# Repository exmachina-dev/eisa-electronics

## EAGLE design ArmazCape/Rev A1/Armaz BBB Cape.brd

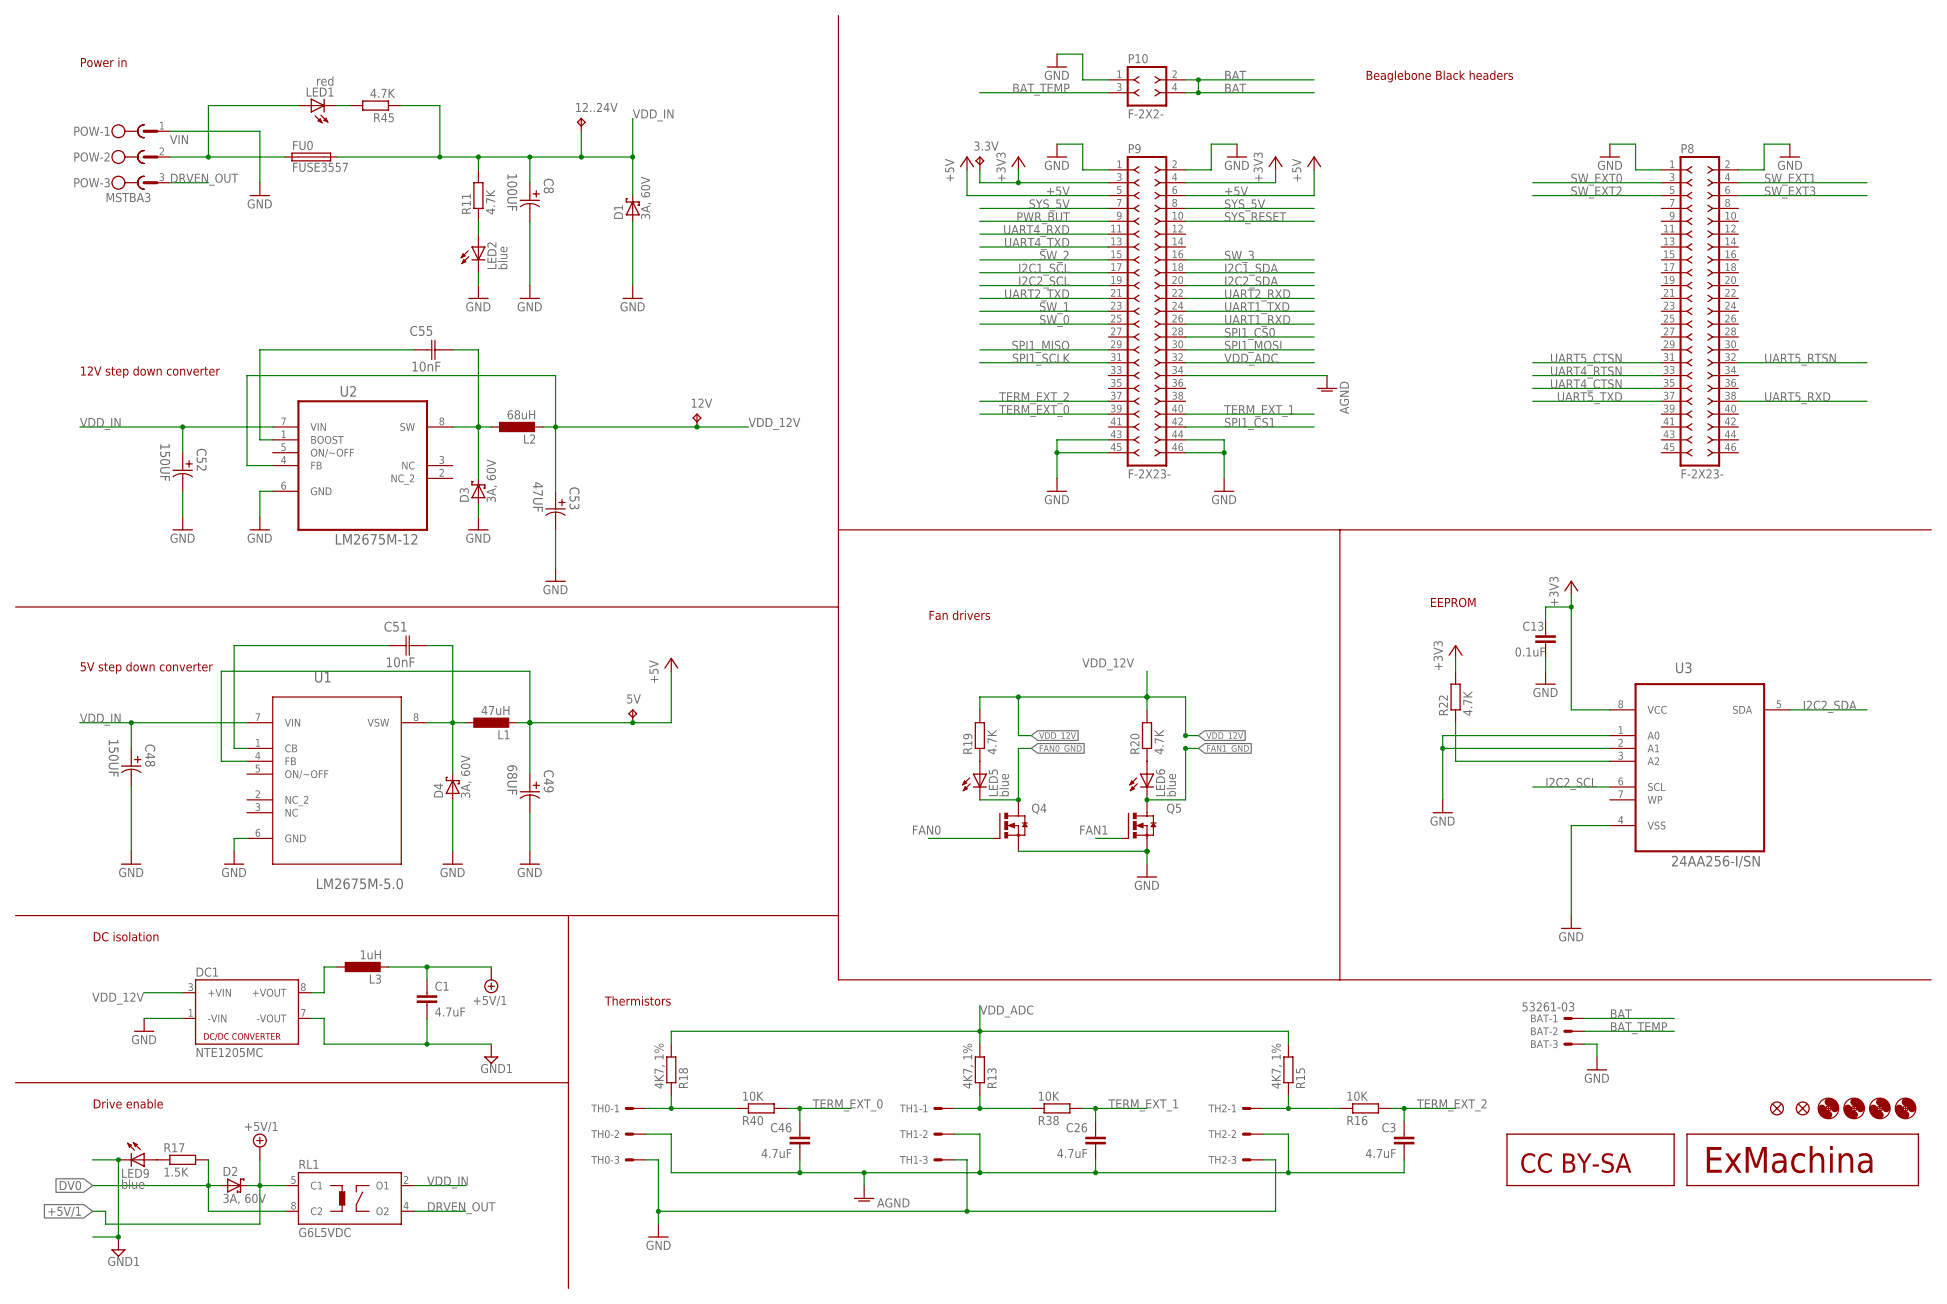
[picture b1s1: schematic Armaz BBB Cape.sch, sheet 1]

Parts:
3.3V, 5V, 12..24V, 12V: TPB1,27; B1,27
BAT: 53261-03; MPN 53261-0371
C1: 4.7uF; C0805; MPN MC0805X475K6R3CT
C3, C26, C46: 4.7uF; C0402; MPN MC0603X475K6R3CT
C8: 100UF; CAPAE660X800N; MPN EEEFTH101XAP
C13: 0.1uF; C0402; MPN MC0402B104K160CT
C48, C52: 150UF; CAPAE660X800N; MPN EEEFTV151XAP
C49: 68UF; CAPAE430X610N; MPN EEEFT1A680AR
C51, C55: 10nF; CAPC2013X90N; MPN MCU0805R103KCT
C53: 47UF; CAPAE530X610N; MPN EEEFT1E470AR
D1, D2, D3, D4: 3A, 60V; SMB
DC1: NTE1205MC; NTE; MPN NTE1205MC
FU0: FUSE3557; 3557; MPN 3557
H1, H2, H3, H4: MOUNT-HOLE3.3; 3,3
JP1, JP2: FIDUCIAL1X2; FIDUCIAL-1X2
L1: 47uH; B82462G4; MPN B82462G4473M
L2: 68uH; B82462G4; MPN B82462G4683M
L3: 1uH; B82462G4; MPN B82462G4102M
LED1: red; CHIP-LED0603; MPN OVS-0608
LED2, LED5, LED6, LED9: blue; CHIP-LED0603; MPN OVS-0603
P8, P9: F-2X23-; DIL-100-2X23; MPN ESQ-123-14-T-D
P10: F-2X2-; DIL-100-2X2; MPN TSW-104-14-T-D
POW: MSTBA3
Q4, Q5: IRLML6344TRPBF; SOT95P240X112-3N
R11, R19, R20, R22, R45: 4.7K; R0402; MPN MCMR04X4701FTL
R13, R15, R18: 4K7, 1%; R0402; MPN MCMR04X4701FTL
R16, R38, R40: 10K; R0402; MPN MCMR04X1002FTL
R17: 1.5K; R0402; MPN MCMR04X1501FTL
RL1: G6L5VDC; G6L-1F; MPN G6L1F5DC
TH0, TH1, TH2: 22-05-7038-03; 7395-03; MPN 22-05-7038
U1: LM2675M-5.0; SOIC127P620X175-8N
U2: LM2675M-12; SOIC127P600X175-8N; MPN LM2675M-12/NOPB
U3: 24AA256-I/SN; SOIC127P600X175-8N
U$1: EXMACHINA-LOGO; EXM-LOGO
U$2: CC-BY-SA

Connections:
$1: C51.1 (C1), U1.1 (CB)
+3V3: 3.3V.TP, C13.1, P9.3, P9.4, R22.2, U3.8 (VCC); also elsewhere on the board
+5V: 5V.TP, C49.1, L1.2, P9.5, P9.6, U1.4 (FB); also elsewhere on the board
+5V/1: C1.1, D2.C, L3.2, RL1.5 (C1); also elsewhere on the board
AGND: C3.2, C26.2, C46.2, P9.34, TH0.2, TH1.2, TH2.2
BAT: BAT.1, P10.2, P10.4
BAT_TEMP: BAT.2, P10.3
DRVEN_OUT: POW.3, RL1.4 (O2)
DV0: D2.A, R17.2, RL1.8 (C2); also elsewhere on the board
FAN0: Q4.1 (G); also elsewhere on the board
FAN0_GND: LED5.C, Q4.3 (D); also elsewhere on the board
FAN1: Q5.1 (G); also elsewhere on the board
FAN1_GND: LED6.C, Q5.3 (D); also elsewhere on the board
GND: BAT.3, C8.2, C13.2, C48.2, C49.2, C52.2, C53.2, D1.A, D3.A, D4.A, DC1.1 (-VIN), LED2.C, P8.1, P8.2, P9.1, P9.2, P9.43, P9.44, P9.45, P9.46, P10.1, POW.1, Q4.2 (S), Q5.2 (S), TH0.3, TH1.3, TH2.3, U2.6 (GND), U3.1 (A0), U3.2 (A1), U3.4 (VSS); also elsewhere on the board
GND1: C1.2, DC1.7 (-VOUT), LED9.C; also elsewhere on the board
I2C1_SCL: P9.17
I2C1_SDA: P9.18
I2C2_SCL: P9.19, U3.6 (SCL); also elsewhere on the board
I2C2_SDA: P9.20, U3.5 (SDA); also elsewhere on the board
unnamed: LED9.A, R17.1
unnamed: LED1.C, R45.2
unnamed: LED5.A, R19.1
unnamed: DC1.8 (+VOUT), L3.1
unnamed: R15.1, R16.1, TH2.1
unnamed: LED2.A, R11.1
unnamed: LED6.A, R20.1
unnamed: R22.1, U3.3 (A2)
unnamed: R13.1, R38.1, TH1.1
unnamed: R18.1, R40.1, TH0.1
unnamed: C55.1 (C1), U2.1 (BOOST)
PWR_BUT: P9.9
SPI1_CS0: P9.28; also elsewhere on the board
SPI1_CS1: P9.42
SPI1_MISO: P9.29; also elsewhere on the board
SPI1_MOSI: P9.30; also elsewhere on the board
SPI1_SCLK: P9.31; also elsewhere on the board
SW: C51.2 (C2), D4.C, L1.1, U1.8 (VSW)
SW_0: P9.25; also elsewhere on the board
SW_1: P9.23; also elsewhere on the board
SW_2: P9.15; also elsewhere on the board
SW_3: P9.16; also elsewhere on the board
SW_12V: C55.2 (C2), D3.C, L2.1, U2.8 (SW)
SW_EXT0: P8.3; also elsewhere on the board
SW_EXT1: P8.4; also elsewhere on the board
SW_EXT2: P8.5; also elsewhere on the board
SW_EXT3: P8.6; also elsewhere on the board
SYS_5V: P9.7, P9.8; also elsewhere on the board
SYS_RESET: P9.10; also elsewhere on the board
TERM_EXT_0: C46.1, P9.39, R40.2
TERM_EXT_1: C26.1, P9.40, R38.2
TERM_EXT_2: C3.1, P9.37, R16.2
UART1_RXD: P9.26
UART1_TXD: P9.24
UART2_RXD: P9.22
UART2_TXD: P9.21
UART4_CTSN: P8.35
UART4_RTSN: P8.33
UART4_RXD: P9.11; also elsewhere on the board
UART4_TXD: P9.13
UART5_CTSN: P8.31
UART5_RTSN: P8.32
UART5_RXD: P8.38; also elsewhere on the board
UART5_TXD: P8.37; also elsewhere on the board
VDD_12V: 12V.TP, C53.1, DC1.3 (+VIN), L2.2, R19.2, R20.2, U2.4 (FB); also elsewhere on the board
VDD_ADC: P9.32, R13.2, R15.2, R18.2
VDD_IN: 12..24V.TP, C8.1, C48.1, C52.1, D1.C, FU0.3 (2), FU0.4 (2), R11.2, R45.1, RL1.2 (O1), U1.7 (VIN), U2.7 (VIN)
VIN: FU0.1, FU0.2 (1), LED1.A, POW.2

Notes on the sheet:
5V step down converter
Power in
12V step down converter
EEPROM
Fan drivers
Thermistors
Drive enable
DC isolation
Beaglebone Black headers

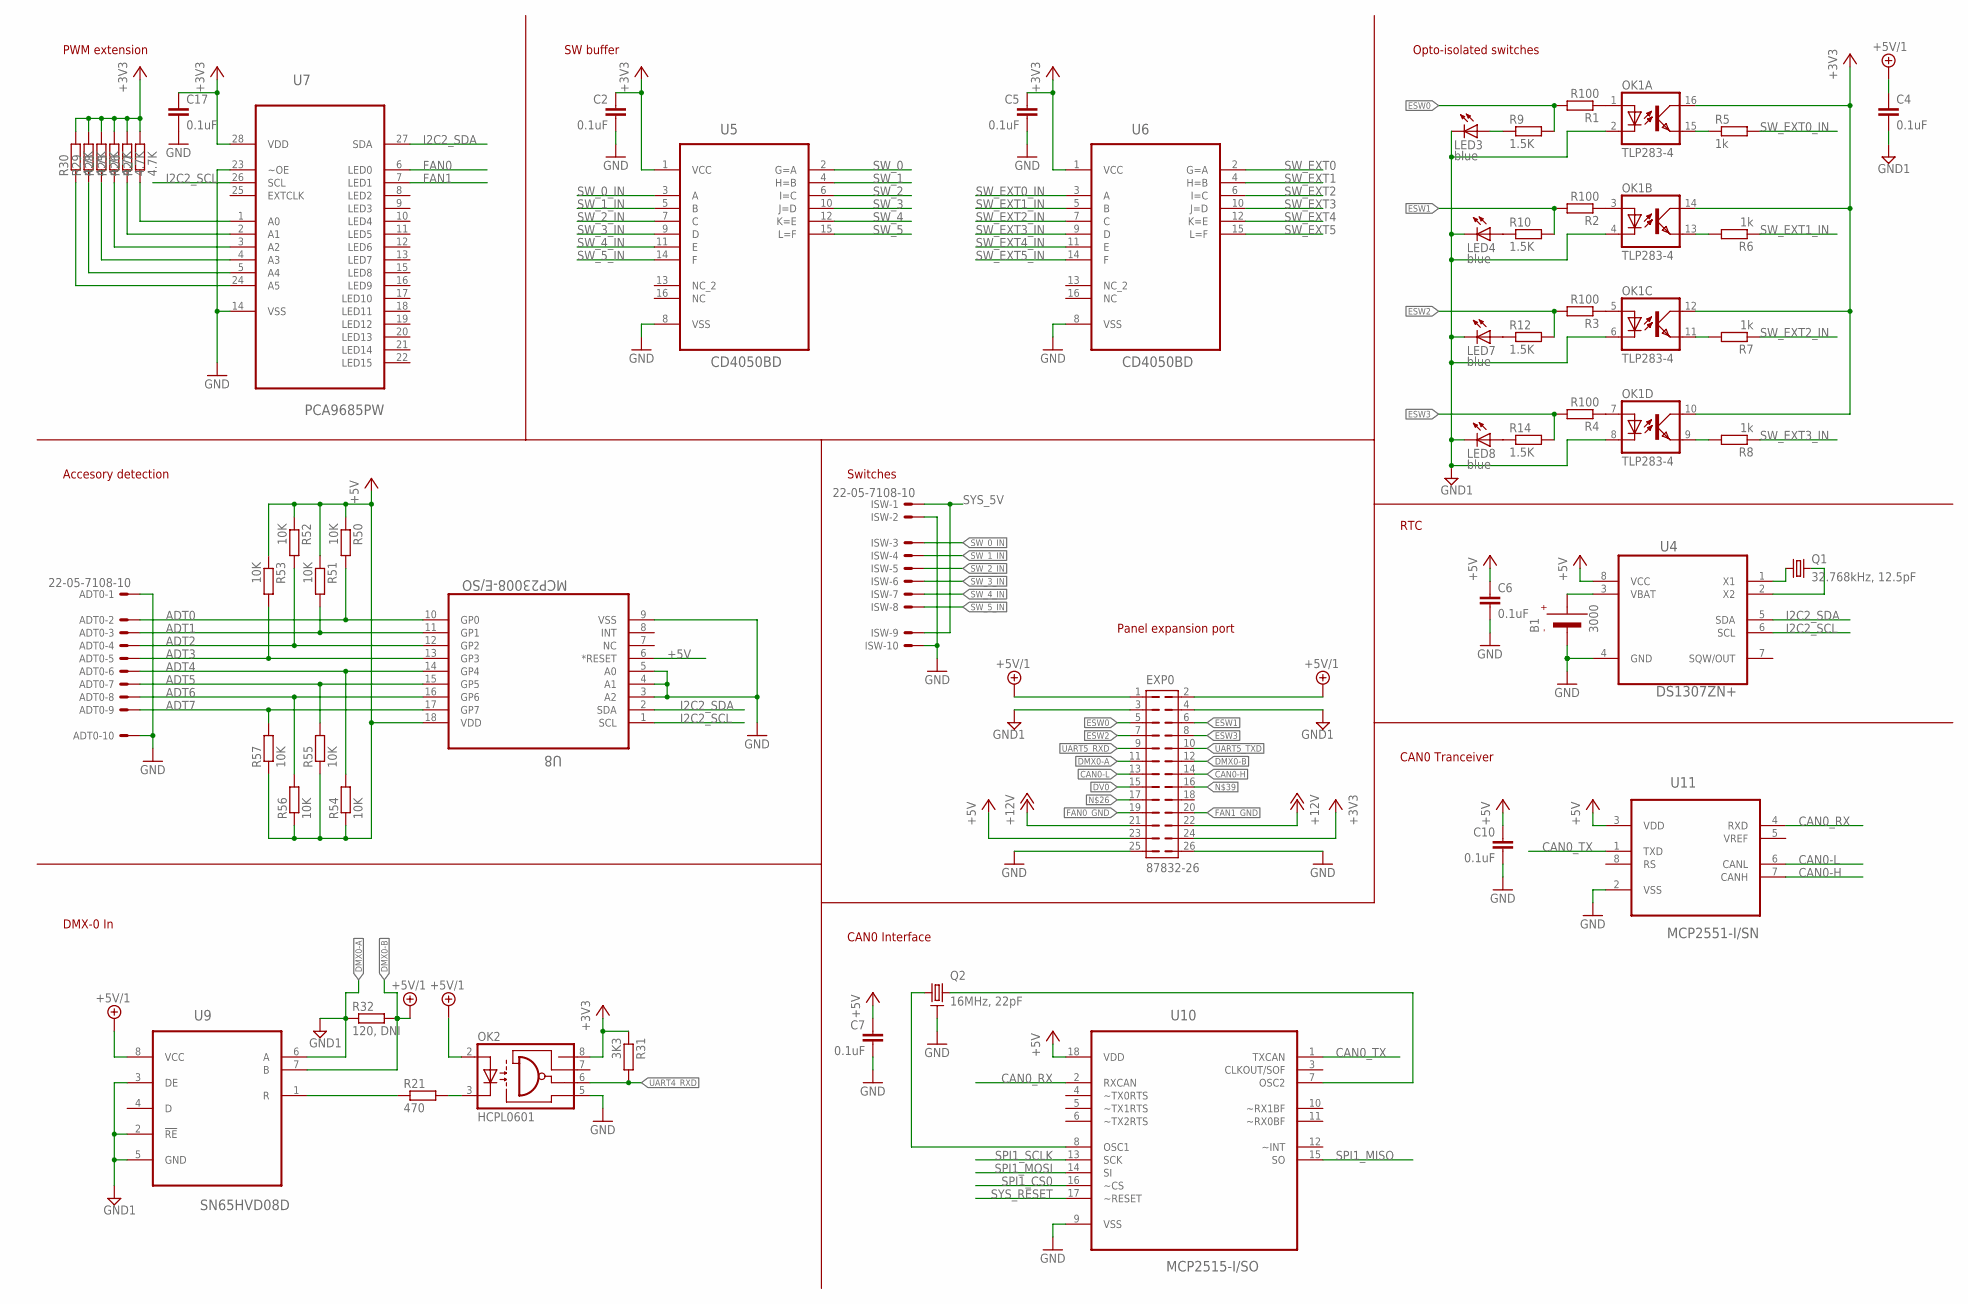
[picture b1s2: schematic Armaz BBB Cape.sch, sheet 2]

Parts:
ADT0: 22-05-7108-10; 7395-10; MPN 22-05-7108
B1: 3000; MPN 3000
C2, C4, C5, C6, C7, C10, C17: 0.1uF; C0402; MPN MC0402B104K160CT
EXP0: 87832-26; MPN 87832-2620
ISW: 22-05-7108-10; 7395-10; MPN 22-05-7108
LED3, LED4, LED7, LED8: blue; CHIP-LED0603; MPN OVS-0603
OK1: TLP283-4; MINI-FLAT-16; MPN TCMT4100
OK2: HCPL0601; SOIC08
Q1: 32.768kHz, 12.5pF; ABS07; MPN ABS07-32.768KHZ-T
Q2: 16MHz, 22pF; AWSCR-MT; MPN AWSCR-16.00MTD-T
R1, R2, R3, R4: R100; R0402; MPN MCMR04X1000FTL
R5, R6, R7, R8: 1k; R0402; MPN MCMR04X1001FTL
R9, R10, R12, R14: 1.5K; R0402; MPN MCMR04X1501FTL
R21: 470; R0402; MPN MCMR04X4700FTL
R25, R26, R27, R28, R29, R30: 4.7K; R0402; MPN MCMR04X4701FTL
R31: 3K3; R0402; MPN MCMR04X3301FTL
R32: 120, DNI; R0402; MPN MCMR04X1200FTL
R50, R51, R52, R53, R54, R55, R56, R57: 10K; R0402; MPN MCMR04X1002FTL
U4: DS1307ZN+; SOIC127P600X175-8N
U5, U6: CD4050BD; SOIC127P600X175-16N
U7: PCA9685PW; SOP65P640X110-28N
U8: MCP23008-E/SO; SOIC127P1030X265-18N
U9: SN65HVD08D; SOIC127P600X175-8N
U10: MCP2515-I/SO; SOIC127P1034X264-18N
U11: MCP2551-I/SN; SOIC127P600X175-8N

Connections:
+3V3: C2.1, C5.1, C17.1, EXP0.24, OK1.10 (COL), OK1.12 (COL), OK1.14 (COL), OK1.16 (COL), OK2.8 (VCC), R25.2, R26.2, R27.2, R28.2, R29.2, R30.2, R31.1, U5.1 (VCC), U6.1 (VCC), U7.28 (VDD); also elsewhere on the board
+5V: C6.1, C7.1, C10.1, EXP0.23, R50.1, R51.1, R52.1, R53.1, R54.1, R55.1, R56.1, R57.1, U4.8 (VCC), U8.6 (*RESET), U8.18 (VDD), U10.18 (VDD), U11.3 (VDD); also elsewhere on the board
+5V/1: C4.1, EXP0.1, EXP0.2, OK2.2 (A), U9.8 (VCC); also elsewhere on the board
ADT0: ADT0.2, R50.2, U8.10 (GP0)
ADT1: ADT0.3, R51.2, U8.11 (GP1)
ADT2: ADT0.4, R52.2, U8.12 (GP2)
ADT3: ADT0.5, R53.2, U8.13 (GP3)
ADT4: ADT0.6, R54.2, U8.14 (GP4)
ADT5: ADT0.7, R55.2, U8.15 (GP5)
ADT6: ADT0.8, R56.2, U8.16 (GP6)
ADT7: ADT0.9, R57.2, U8.17 (GP7)
CAN0-H: EXP0.14, U11.7 (CANH)
CAN0-L: EXP0.13, U11.6 (CANL)
CAN0_RX: U10.2 (RXCAN), U11.4 (RXD)
CAN0_TX: U10.1 (TXCAN), U11.1 (TXD)
DMX0-A: EXP0.11, R32.1, U9.6 (A)
DMX0-B: EXP0.12, R32.2, U9.7 (B)
DV0: EXP0.15; also elsewhere on the board
ESW0: EXP0.5, R1.2, R9.2
ESW1: EXP0.6, R2.2, R10.2
ESW2: EXP0.7, R3.2, R12.2
ESW3: EXP0.8, R4.2, R14.2
FAN0: U7.6 (LED0); also elsewhere on the board
FAN0_GND: EXP0.19; also elsewhere on the board
FAN1: U7.7 (LED1); also elsewhere on the board
FAN1_GND: EXP0.20; also elsewhere on the board
GND: ADT0.1, ADT0.10, B1.- (VBAT-), C2.2, C5.2, C6.2, C7.2, C10.2, C17.2, EXP0.25, EXP0.26, ISW.2, ISW.10, OK2.5 (GND), Q2.2, U4.4 (GND), U5.8 (VSS), U6.8 (VSS), U7.14 (VSS), U7.23 (~OE), U8.3 (A2), U8.4 (A1), U8.5 (A0), U8.9 (VSS), U10.9 (VSS), U11.2 (VSS); also elsewhere on the board
GND1: C4.2, EXP0.3, EXP0.4, LED3.C, LED4.C, LED7.C, LED8.C, OK1.2 (C), OK1.4 (C), OK1.6 (C), OK1.8 (C), U9.2 (!RE), U9.3 (DE), U9.5 (GND); also elsewhere on the board
I2C2_SCL: U4.6 (SCL), U7.26 (SCL), U8.1 (SCL); also elsewhere on the board
I2C2_SDA: U4.5 (SDA), U7.27 (SDA), U8.2 (SDA); also elsewhere on the board
unnamed: OK1.1 (A), R1.1
unnamed: OK1.3 (A), R2.1
unnamed: OK1.15 (EMIT), R5.1
unnamed: OK1.7 (A), R4.1
unnamed: Q1.P$1 (1), U4.1 (X1)
unnamed: OK1.5 (A), R3.1
unnamed: Q1.P$2 (2), U4.2 (X2)
unnamed: R21.1, U9.1 (R)
unnamed: OK1.9 (EMIT), R8.2
unnamed: OK1.11 (EMIT), R7.2
unnamed: OK1.13 (EMIT), R6.2
unnamed: LED3.A, R9.1
unnamed: OK2.3 (C), R21.2
unnamed: LED4.A, R10.1
unnamed: LED7.A, R12.1
unnamed: LED8.A, R14.1
unnamed: Q2.3, U10.7 (OSC2)
unnamed: Q2.1, U10.8 (OSC1)
unnamed: R27.1, U7.1 (A0)
unnamed: R26.1, U7.2 (A1)
unnamed: R25.1, U7.3 (A2)
unnamed: R28.1, U7.4 (A3)
unnamed: R29.1, U7.5 (A4)
unnamed: R30.1, U7.24 (A5)
SPI1_CS0: U10.16 (~CS); also elsewhere on the board
SPI1_MISO: U10.15 (SO); also elsewhere on the board
SPI1_MOSI: U10.14 (SI); also elsewhere on the board
SPI1_SCLK: U10.13 (SCK); also elsewhere on the board
SW_0: U5.2 (G=A); also elsewhere on the board
SW_0_IN: ISW.3, U5.3 (A)
SW_1: U5.4 (H=B); also elsewhere on the board
SW_1_IN: ISW.4, U5.5 (B)
SW_2: U5.6 (I=C); also elsewhere on the board
SW_2_IN: ISW.5, U5.7 (C)
SW_3: U5.10 (J=D); also elsewhere on the board
SW_3_IN: ISW.6, U5.9 (D)
SW_4: U5.12 (K=E)
SW_4_IN: ISW.7, U5.11 (E)
SW_5: U5.15 (L=F)
SW_5_IN: ISW.8, U5.14 (F)
SW_EXT0: U6.2 (G=A); also elsewhere on the board
SW_EXT0_IN: R5.2, U6.3 (A)
SW_EXT1: U6.4 (H=B); also elsewhere on the board
SW_EXT1_IN: R6.1, U6.5 (B)
SW_EXT2: U6.6 (I=C); also elsewhere on the board
SW_EXT2_IN: R7.1, U6.7 (C)
SW_EXT3: U6.10 (J=D); also elsewhere on the board
SW_EXT3_IN: R8.1, U6.9 (D)
SW_EXT4: U6.12 (K=E)
SW_EXT4_IN: U6.11 (E)
SW_EXT5: U6.15 (L=F)
SW_EXT5_IN: U6.14 (F)
SYS_5V: ISW.1, ISW.9; also elsewhere on the board
SYS_RESET: U10.17 (~RESET); also elsewhere on the board
UART4_RXD: OK2.6 (VO), R31.2; also elsewhere on the board
UART5_RXD: EXP0.9; also elsewhere on the board
UART5_TXD: EXP0.10; also elsewhere on the board
VBAT+: B1.+1 (VBAT+), B1.+2 (VBAT+), U4.3 (VBAT)
VDD_12V: EXP0.21, EXP0.22; also elsewhere on the board

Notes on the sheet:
Switches
PWM extension
SW buffer
Accesory detection
Opto-isolated switches
Panel expansion port
DMX-0 In
RTC
CAN0 Interface
CAN0 Tranceiver

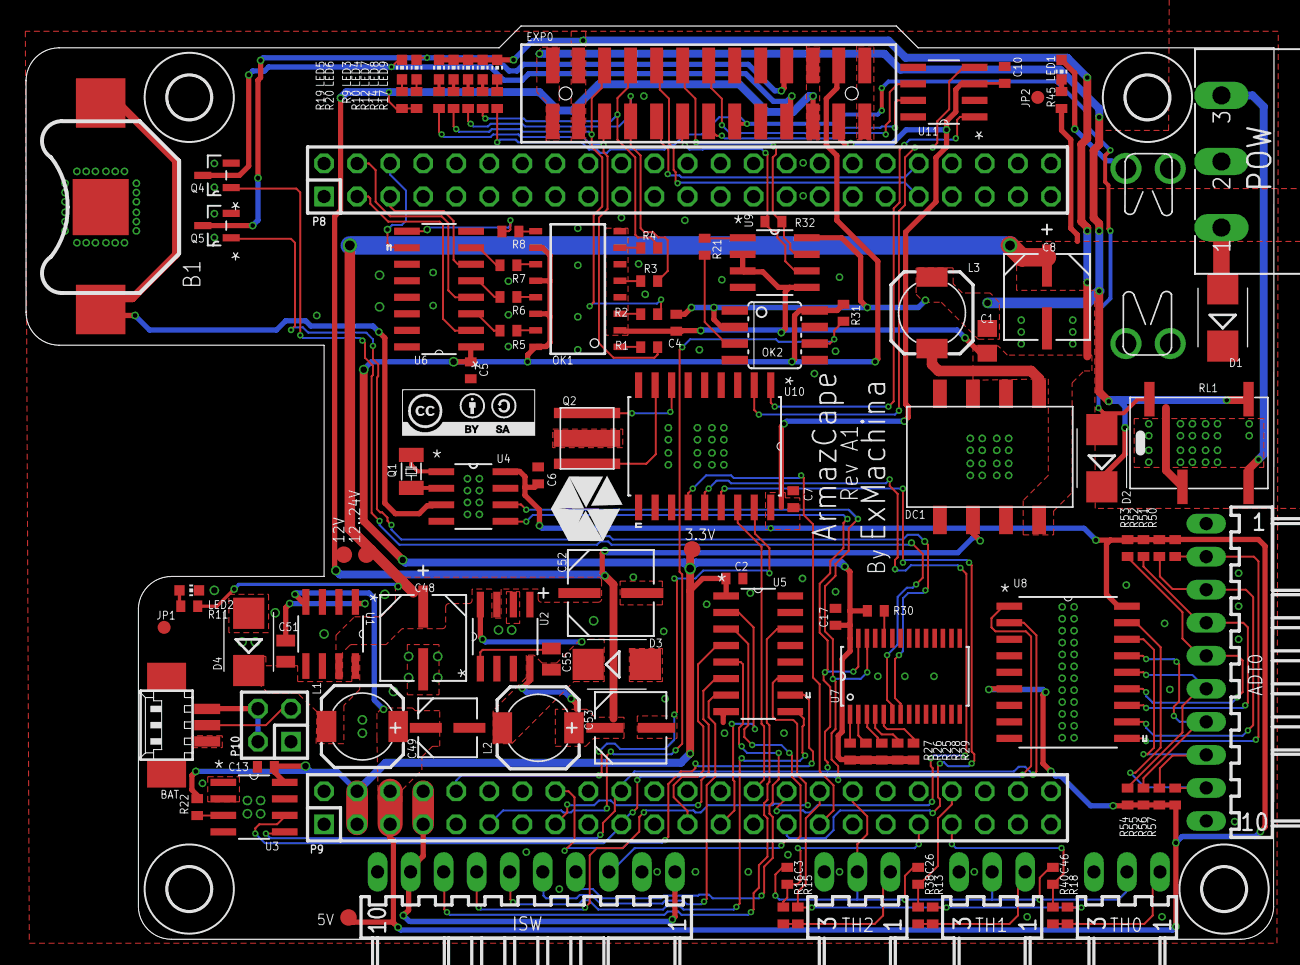
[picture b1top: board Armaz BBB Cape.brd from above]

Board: 2 copper layers, 95.9 x 70.2 mm, 120 parts (0 on the bottom side), 107 nets.

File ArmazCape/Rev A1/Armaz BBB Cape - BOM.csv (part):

"Part";"Value";"Device";"Package";"Description";"MF";"MPN";"OC_FARNELL";"OC_NEWARK";"PACKAGE";"SUPPLIER";"TOLERANCE";"TP_SIGNAL_NAME";"VALUE";"VOLTAGERATING";
"3.3V";"TPB1,27";"TPB1,27";"B1,27";"Test pad";"";"";"unknown";"";"";"";"";"";"";"";
"5V";"TPB1,27";"TPB1,27";"B1,27";"Test pad";"";"";"unknown";"";"";"";"";"";"";"";
"12..24V";"TPB1,27";"TPB1,27";"B1,27";"Test pad";"";"";"unknown";"";"";"";"";"";"";"";
"12V";"TPB1,27";"TPB1,27";"B1,27";"Test pad";"";"";"unknown";"";"";"";"";"";"";"";
"ADT0";"22-05-7108-10";"22-05-7108-10";"7395-10";"CONNECTOR";"MOLEX";"22-05-7108";"9731660";"unknown";"";"";"";"";"";"";
"B1";"3000";"3000";"3000";"";"KEYSTONE";"3000";"1650692";"";"";"";"";"";"";"";
"BAT";"53261-03";"53261-03";"53261-03";"CONNECTOR";"MOLEX";"53261-0371";"1125359";"57H5006";"";"";"";"";"";"";
"C1";"4.7uF";"C-EUC0805";"C0805";"CAPACITOR, European symbol";"MULTICOMP";"MC0805X475K6R3CT";"1759414";"";"";"";"";"";"";"";
"C2";"0.1uF";"C-EUC0402";"C0402";"CAPACITOR, European symbol";"MULTICOMP";"MC0402B104K160CT";"1758896";"";"";"";"";"";"";"";
"C3";"4.7uF";"C-EUC0402";"C0402";"CAPACITOR, European symbol";"MULTICOMP";"MC0603X475K6R3CT";"2320811";"";"";"";"";"";"";"";
"C4";"0.1uF";"C-EUC0402";"C0402";"CAPACITOR, European symbol";"MULTICOMP";"MC0402B104K160CT";"1758896";"";"";"";"";"";"";"";
"C5";"0.1uF";"C-EUC0402";"C0402";"CAPACITOR, European symbol";"MULTICOMP";"MC0402B104K160CT";"1758896";"";"";"";"";"";"";"";
"C6";"0.1uF";"C-EUC0402";"C0402";"CAPACITOR, European symbol";"MULTICOMP";"MC0402B104K160CT";"1758896";"";"";"";"";"";"";"";
"C7";"0.1uF";"C-EUC0402";"C0402";"CAPACITOR, European symbol";"MULTICOMP";"MC0402B104K160CT";"1758896";"";"";"";"";"";"";"";
"C8";"100UF";"EEE-FTH101XAP-CASE-D8";"CAPAE660X800N";"Aluminum Electrolytic Capacitors,Surface Mount Type";"PANASONIC ELECTRONIC COMPONENTS";"EEEFTH101XAP";"1868426";"31T8172";"CASE-D8";"PANASONIC";"±20 %";"";"100UF";"50V";
"C10";"0.1uF";"C-EUC0402";"C0402";"CAPACITOR, European symbol";"MULTICOMP";"MC0402B104K160CT";"1758896";"";"";"";"";"";"";"";
"C13";"0.1uF";"C-EUC0402";"C0402";"CAPACITOR, European symbol";"MULTICOMP";"MC0402B104K160CT";"1758896";"";"";"";"";"";"";"";
"C17";"0.1uF";"C-EUC0402";"C0402";"CAPACITOR, European symbol";"MULTICOMP";"MC0402B104K160CT";"1758896";"";"";"";"";"";"";"";
"C26";"4.7uF";"C-EUC0402";"C0402";"CAPACITOR, European symbol";"MULTICOMP";"MC0603X475K6R3CT";"2320811";"";"";"";"";"";"";"";
"C46";"4.7uF";"C-EUC0402";"C0402";"CAPACITOR, European symbol";"MULTICOMP";"MC0603X475K6R3CT";"2320811";"";"";"";"";"";"";"";
"C48";"150UF";"EEE-FTV151XAP-CASE-D8";"CAPAE660X800N";"Aluminum Electrolytic Capacitors,Surface Mount Type";"PANASONIC ELECTRONIC COMPONENTS";"EEEFTV151XAP";"1868418";"31T8173";"CASE-D8";"PANASONIC";"±20 %";"";"150UF";"35V";
"C49";" 68UF";"EEE-FT1A680AR-CASE-B";"CAPAE430X610N";"Aluminum Electrolytic Capacitors,Surface Mount Type";"PANASONIC ELECTRONIC COMPONENTS";"EEEFT1A680AR";"2065959";"73T9155";"CASE-B";"PANASONIC";"±20 %";"";" 68UF";"10V";
"C51";"10nF";"U0805R103KCT";"CAPC2013X90N";"CAPACITOR, 0805";"MULTICOMP";"MCU0805R103KCT";"9406352";"38K9283";"";"Multicomp";"±10%";"";"10nF";"50V";
"C52";"150UF";"EEE-FTV151XAP-CASE-D8";"CAPAE660X800N";"Aluminum Electrolytic Capacitors,Surface Mount Type";"PANASONIC ELECTRONIC COMPONENTS";"EEEFTV151XAP";"1868418";"31T8173";"CASE-D8";"PANASONIC";"±20 %";"";"150UF";"35V";
"C53";" 47UF";"EEE-FT1E470AR-CASE-C";"CAPAE530X610N";"Aluminum Electrolytic Capacitors,Surface Mount Type";"PANASONIC ELECTRONIC COMPONENTS";"EEEFT1E470AR";"1868404";"31T8177";"CASE-C";"PANASONIC";"±20 %";"";" 47UF";"25V";
"C55";"10nF";"U0805R103KCT";"CAPC2013X90N";"CAPACITOR, 0805";"MULTICOMP";"MCU0805R103KCT";"9406352";"38K9283";"";"Multicomp";"±10%";"";"10nF";"50V";
"D1";"3A, 60V";"MBRS360BT3G";"SMB";"";"ON SEMICONDUCTOR";"MBRS360BT3G";"2317398";"";"";"ON SEMICONDUCTOR";"";"";"3A, 60V";"";
"D2";"3A, 60V";"MBRS360BT3G";"SMB";"";"ON SEMICONDUCTOR";"MBRS360BT3G";"2317398";"";"";"ON SEMICONDUCTOR";"";"";"3A, 60V";"";
"D3";"3A, 60V";"MBRS360BT3G";"SMB";"";"ON SEMICONDUCTOR";"MBRS360BT3G";"2317398";"";"";"ON SEMICONDUCTOR";"";"";"3A, 60V";"";
"D4";"3A, 60V";"MBRS360BT3G";"SMB";"";"ON SEMICONDUCTOR";"MBRS360BT3G";"2317398";"";"";"ON SEMICONDUCTOR";"";"";"3A, 60V";"";
"DC1";"NTE1205MC";"NTE1205MC";"NTE";"";"MURATA POWER SOLUTIONS";"NTE1205MC";"1021603";"";"";"";"";"";"";"";
"EXP0";"87832-26";"87832-26";"87832-26";"Milli-Grid Header";"MOLEX";"87832-2620";"2313712";"unknown";"";"";"";"";"";"";
"FU0";"FUSE3557";"FUSE3557";"3557";"Fuse";"KEYSTONE";"3557";"2292902";"";"";"";"";"";"";"";
"H1";"MOUNT-HOLE3.3";"MOUNT-HOLE3.3";"3,3";"MOUNTING HOLE with drill center marker";"";"";"unknown";"";"";"";"";"";"";"";
"H2";"MOUNT-HOLE3.3";"MOUNT-HOLE3.3";"3,3";"MOUNTING HOLE with drill center marker";"";"";"unknown";"";"";"";"";"";"";"";
"H3";"MOUNT-HOLE3.3";"MOUNT-HOLE3.3";"3,3";"MOUNTING HOLE with drill center marker";"";"";"unknown";"";"";"";"";"";"";"";
"H4";"MOUNT-HOLE3.3";"MOUNT-HOLE3.3";"3,3";"MOUNTING HOLE with drill center marker";"";"";"unknown";"";"";"";"";"";"";"";
"ISW";"22-05-7108-10";"22-05-7108-10";"7395-10";"CONNECTOR";"MOLEX";"22-05-7108";"9731660";"unknown";"";"";"";"";"";"";
"JP1";"FIDUCIAL1X2";"FIDUCIAL1X2";"FIDUCIAL-1X2";"Fiducial Alignment Points";"";"";"unknown";"";"";"";"";"";"";"";
"JP2";"FIDUCIAL1X2";"FIDUCIAL1X2";"FIDUCIAL-1X2";"Fiducial Alignment Points";"";"";"unknown";"";"";"";"";"";"";"";
"L1";"47uH";"B82462G4473M000";"B82462G4";"";"EPCOS";"B82462G4473M";"7430060";"";"";"";"";"";"47uH";"";
"L2";"68uH";"B82462G4683M000";"B82462G4";"";"EPCOS";"B82462G4683M";"7430078";"";"";"";"";"";"68uH";"";
"L3";"1uH";"B82462G4102M000";"B82462G4";"";"EPCOS";"B82462G4102M";"7429967";"";"";"";"";"";"1uH";"";
"LED1";"red";"LEDCHIP-LED0603";"CHIP-LED0603";"LED";"MULTICOMP";"OVS-0608";"1716774";"";"";"";"";"";"";"";
"LED2";"blue";"LEDCHIP-LED0603";"CHIP-LED0603";"LED";"MULTICOMP";"OVS-0603";"1716770";"";"";"";"";"";"";"";
"LED3";"blue";"LEDCHIP-LED0603";"CHIP-LED0603";"LED";"MULTICOMP";"OVS-0603";"1716770";"";"";"";"";"";"";"";
"LED4";"blue";"LEDCHIP-LED0603";"CHIP-LED0603";"LED";"MULTICOMP";"OVS-0603";"1716770";"";"";"";"";"";"";"";
"LED5";"blue";"LEDCHIP-LED0603";"CHIP-LED0603";"LED";"MULTICOMP";"OVS-0603";"1716770";"";"";"";"";"";"";"";
"LED6";"blue";"LEDCHIP-LED0603";"CHIP-LED0603";"LED";"MULTICOMP";"OVS-0603";"1716770";"";"";"";"";"";"";"";
"LED7";"blue";"LEDCHIP-LED0603";"CHIP-LED0603";"LED";"MULTICOMP";"OVS-0603";"1716770";"";"";"";"";"";"";"";
"LED8";"blue";"LEDCHIP-LED0603";"CHIP-LED0603";"LED";"MULTICOMP";"OVS-0603";"1716770";"";"";"";"";"";"";"";
"LED9";"blue";"LEDCHIP-LED0603";"CHIP-LED0603";"LED";"MULTICOMP";"OVS-0603";"1716770";"";"";"";"";"";"";"";
"OK1";"TLP283-4";"TLP283-4";"MINI-FLAT-16";"TOSHIBA PHOTOCOUPLER GaAs IRED & PHOTO-TRANSISTOR";"VISHAY";"TCMT4100";"1779650";"unknown";"";"";"";"";"";"";
"OK2";"HCPL0601";"HCPL0601";"SOIC08";"HEWLETT PACKARD OPTO COUPLER";"AVAGO TECHNOLOGIES";"HCPL-0601-000E";"9995102";"88H7776";"";"";"";"";"";"";
"P8";"F-2X23-";"F-2X23-";"DIL-100-2X23";"";"SAMTEC";"ESQ-123-14-T-D";"1932255";"";"";"";"";"";"";"";
"P9";"F-2X23-";"F-2X23-";"DIL-100-2X23";"";"SAMTEC";"ESQ-123-14-T-D";"1932255";"";"";"";"";"";"";"";
"P10";"F-2X2-";"F-2X2-";"DIL-100-2X2";"";"SAMTEC";"TSW-104-14-T-D";"2027226";"";"";"";"";"";"";"";
"POW";"MSTBA3";"MSTBA3";"MSTBA3";"PHOENIX";"PHOENIX CONTACT";"1757255";"3705183";"71C4162";"";"";"";"";"";"";
"Q1";"32.768kHz, 12.5pF";"ABS07-32.768KHZ";"ABS07";"";"ABRACON";"ABS07-32.768KHZ-T";"2101347";"";"";"";"";"";"32.768kHz, 12.5pF";"";
"Q2";"16MHz, 22pF";"AWSCR-16MHZ-MTD-C22PF";"AWSCR-MT";"";"ABRACON";"AWSCR-16.00MTD-T";"2101362";"";"";"";"";"";"16MHz, 22pF";"";
"Q4";"";"IRLML6344TRPBF";"SOT95P240X112-3N";"Power MOSFET";"INTERNATIONAL RECTIFIER";"IRLML6344TRPBF";"1857299";"25T5501";"SOT-23-3";"INTERNATIONAL RECTIFIER";"";"";"";"";
"Q5";"";"IRLML6344TRPBF";"SOT95P240X112-3N";"Power MOSFET";"INTERNATIONAL RECTIFIER";"IRLML6344TRPBF";"1857299";"25T5501";"SOT-23-3";"INTERNATIONAL RECTIFIER";"";"";"";"";
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
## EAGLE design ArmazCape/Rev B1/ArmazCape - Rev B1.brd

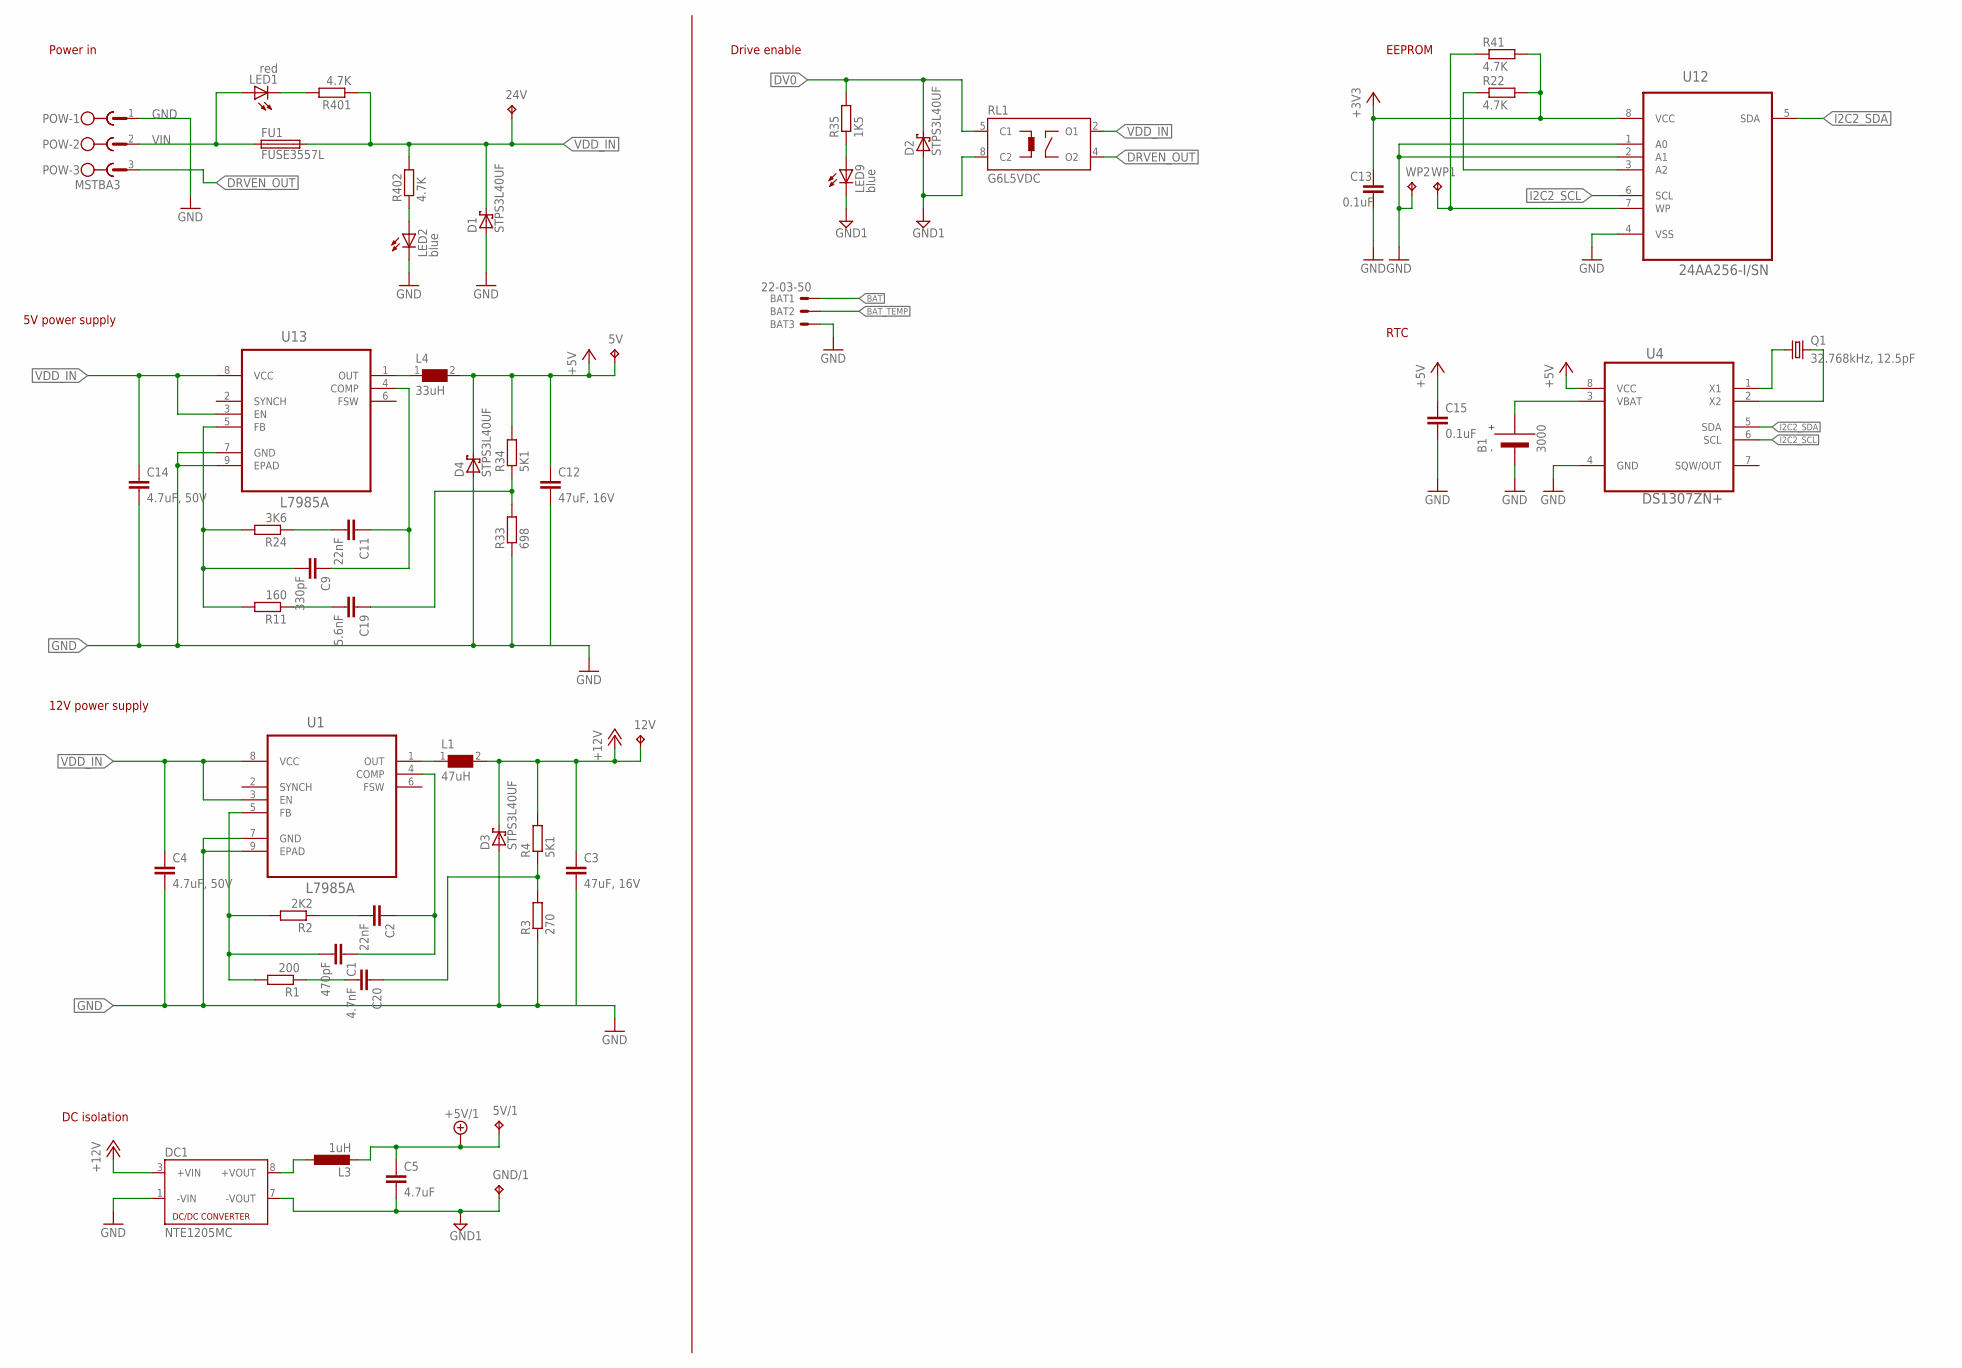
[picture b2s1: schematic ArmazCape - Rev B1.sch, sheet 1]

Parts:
5V, 5V/1, 12V, 24V: TPB1,27; B1,27
B1: 3000; MPN 3000
BAT: 22-03-50; 5267-02A; MPN 22-03-5035
C1: 470pF; C0603; MPN GRM188R71H471KA01D
C2, C11: 22nF; C0603; MPN GRM188R71E223KA01D
C3, C12: 47uF, 16V; C1210; MPN GRM32ER61C476ME15L
C4, C14: 4.7uF, 50V; C1210; MPN GRM32ER71H475KA88L
C5: 4.7uF; C0805; MPN MC0805X475K6R3CT
C9: 330pF; C0603; MPN GRM1885C1H331JA01D
C13, C15: 0.1uF; C0603; MPN MC0603B104K250CT
C19: 5.6nF; C0603; MPN MC0603B562K500CT
C20: 4.7nF; C0603; MPN GRM188R71H472KA01D
D1, D2, D3, D4: STPS3L40UF; SMB
DC1: NTE1205MC; NTE; MPN NTE1205MC
FU1: FUSE3557L; 3557-LITTLE; MPN 3557
GND/1: TPB1,27; B1,27
L1: 47uH; WE-PD_1260/1245/1280/1210
L3: 1uH; B82462G4; MPN B82462G4102M
L4: 33uH; WE-PD_1260/1245/1280/1210
LED1: red; CHIP-LED0603; MPN OVS-0608
LED2, LED9: blue; CHIP-LED0603; MPN OVS-0603
POW: MSTBA3
Q1: 32.768kHz, 12.5pF; ABS07; MPN ABS07-32.768KHZ-T
R1: 200; R0603; MPN MCMR06X2000FTL
R2: 2K2; R0603; MPN MCMR06X2201FTL
R3: 270; R0603; MPN MCMR06X2000FTL
R4, R34: 5K1; R0603; MPN MCMR06X5101FTL
R11: 160; R0603; MPN MCMR04X1600FTL
R22, R41, R401, R402: 4.7K; R0603; MPN MCMR06X4701FTL
R24: 3K6; R0603; MPN MCMR06X3601FTL
R33: 698; R0603; MPN MCMR04X6980FTL
R35: 1K5; R0603; MPN MCMR06X1501FTL
RL1: G6L5VDC; G6L-1F; MPN G6L1F5DC
U1, U13: L7985A; SOIC127P600X170-9N
U4: DS1307ZN+; SOIC127P600X175-8N
U12: 24AA256-I/SN; SOIC127P600X175-8N
WP1, WP2: TPB1,27; B1,27

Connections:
+3V3: C13.1, R22.2, R41.2, U12.8 (VCC); also elsewhere on the board
+5V: 5V.TP, C12.1, C15.1, D4.C, L4.2, R34.2, U4.8 (VCC); also elsewhere on the board
+5V/1: 5V/1.TP, C5.1, L3.2; also elsewhere on the board
+12V: 12V.TP, C3.1, D3.C, DC1.3 (+VIN), L1.2, R4.2; also elsewhere on the board
BAT: BAT.P1; also elsewhere on the board
BAT_TEMP: BAT.P2; also elsewhere on the board
DRVEN_OUT: POW.3, RL1.4 (O2)
DV0: D2.C, R35.2, RL1.5 (C1); also elsewhere on the board
GND: B1.- (VBAT-), BAT.P3, C3.2, C4.2, C12.2, C13.2, C14.2, C15.2, D1.A, D3.A, D4.A, DC1.1 (-VIN), LED2.C, POW.1, R3.1, R33.1, U1.7 (GND), U1.9 (EPAD), U4.4 (GND), U12.1 (A0), U12.2 (A1), U12.4 (VSS), U13.7 (GND), U13.9 (EPAD), WP2.TP; also elsewhere on the board
GND1: C5.2, D2.A, DC1.7 (-VOUT), GND/1.TP, LED9.C, RL1.8 (C2); also elsewhere on the board
I2C2_SCL: U4.6 (SCL), U12.6 (SCL); also elsewhere on the board
I2C2_SDA: U4.5 (SDA), U12.5 (SDA); also elsewhere on the board
unnamed: C9.2, R11.2, R24.2, U13.5 (FB)
unnamed: C2.2, R2.1
unnamed: C1.1, C2.1, U1.4 (COMP)
unnamed: C1.2, R1.2, R2.2, U1.5 (FB)
unnamed: L1.1, U1.1 (OUT)
unnamed: LED9.A, R35.1
unnamed: LED1.C, R401.2
unnamed: L4.1, U13.1 (OUT)
unnamed: DC1.8 (+VOUT), L3.1
unnamed: Q1.1, U4.1 (X1)
unnamed: Q1.2, U4.2 (X2)
unnamed: C11.2, R24.1
unnamed: C9.1, C11.1, U13.4 (COMP)
unnamed: C19.1, R33.2, R34.1
unnamed: C19.2, R11.1
unnamed: C20.2, R1.1
unnamed: R41.1, U12.7 (WP), WP1.TP
unnamed: R22.1, U12.3 (A2)
unnamed: C20.1, R3.2, R4.1
unnamed: LED2.A, R402.1
VBAT+: B1.+1 (VBAT+), B1.+2 (VBAT+), U4.3 (VBAT)
VDD_IN: 24V.TP, C4.1, C14.1, D1.C, FU1.3 (2), FU1.4 (2), R401.1, R402.2, RL1.2 (O1), U1.3 (EN), U1.8 (VCC), U13.3 (EN), U13.8 (VCC)
VIN: FU1.1, FU1.2 (1), LED1.A, POW.2

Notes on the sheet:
Power in
5V power supply
12V power supply
DC isolation
Drive enable
EEPROM
RTC

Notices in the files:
ArmazCape/Rev A1/Armaz BBB Cape - BOM.csv:
"CC-BY-SA";"CC-BY-SA";"CC-BY-SA";"";"";"";"unknown";"";"";"";"";"";"";"";
ArmazCape/Rev B1/ArmazCape - Rev B1.brd:
Creatives Commons
CC BY-SA
